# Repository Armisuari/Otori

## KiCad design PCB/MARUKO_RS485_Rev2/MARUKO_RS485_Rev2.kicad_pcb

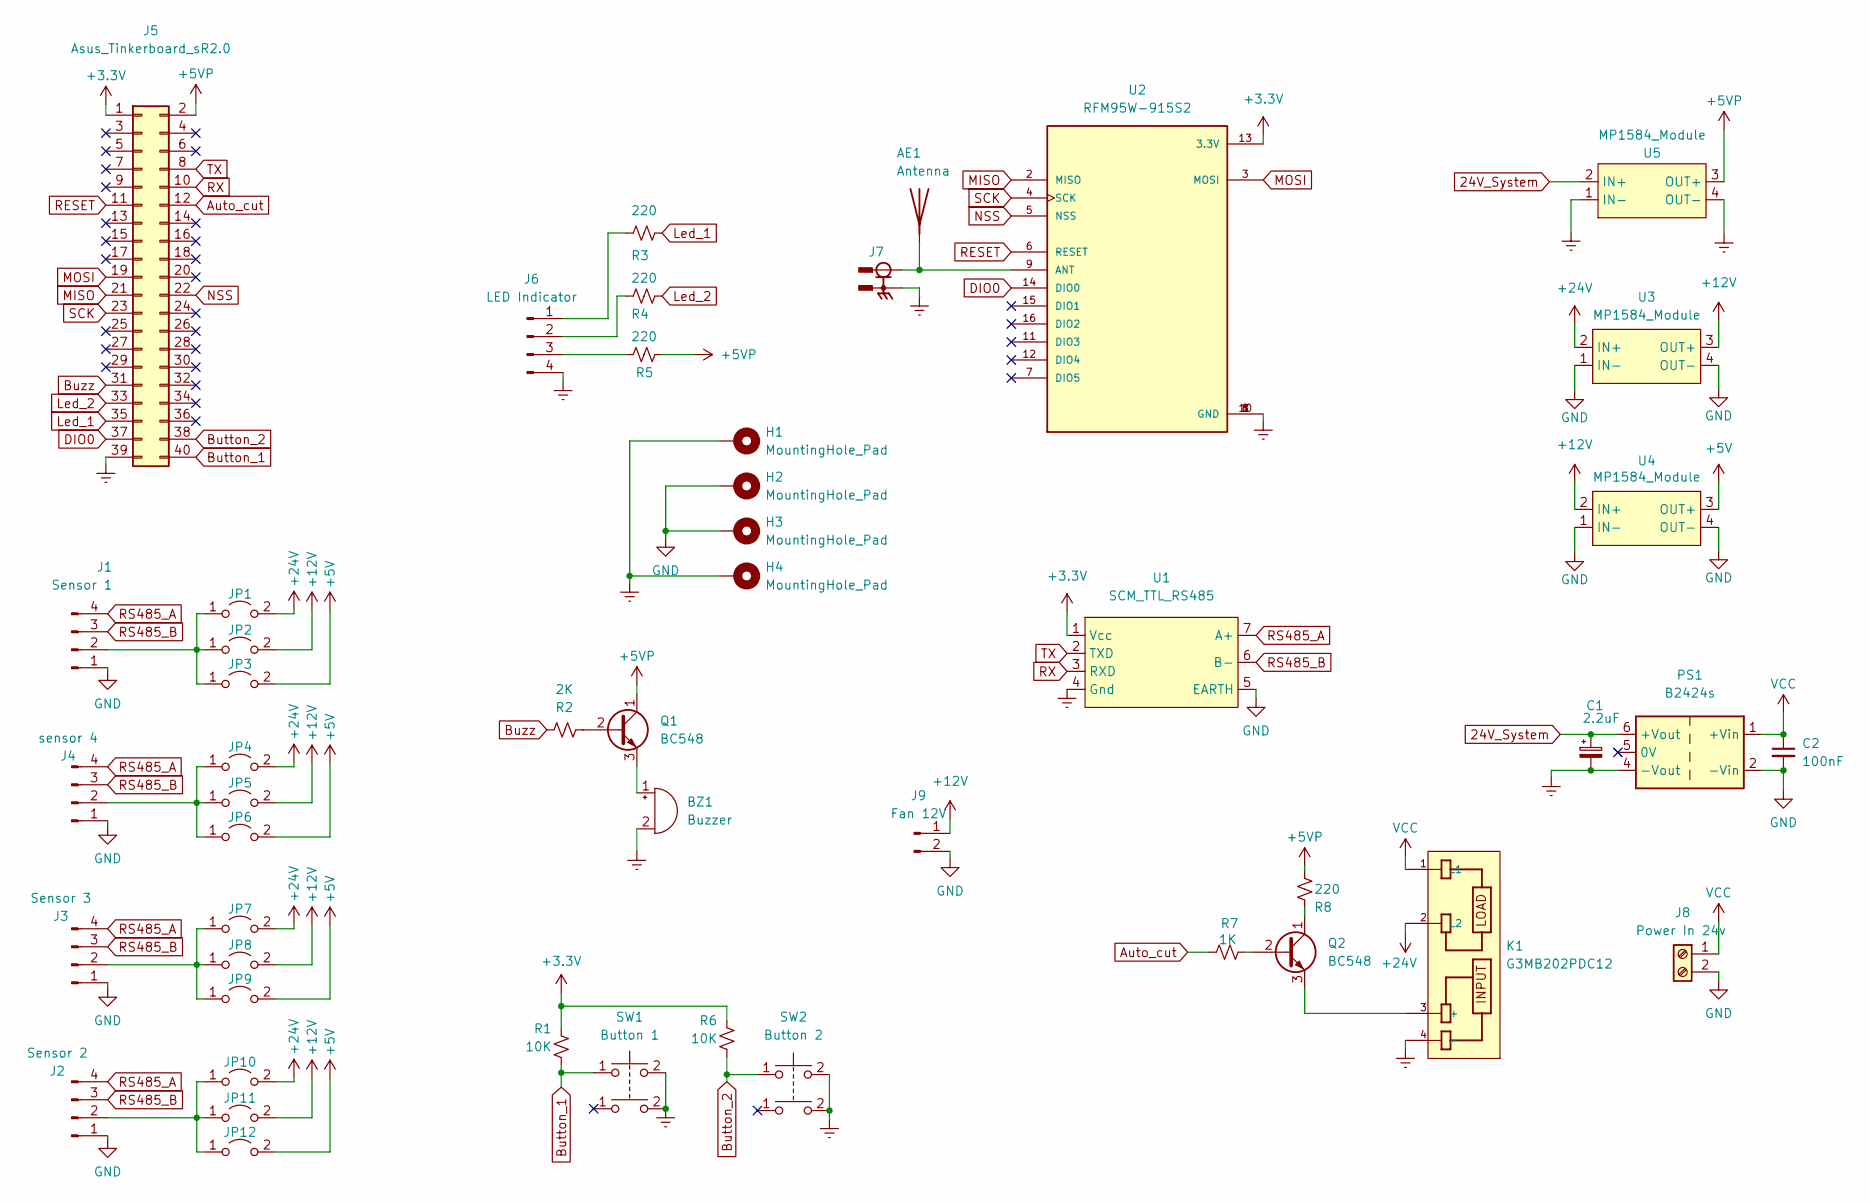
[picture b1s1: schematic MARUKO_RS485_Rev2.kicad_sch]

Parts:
AE1: Antenna
BZ1: Buzzer; Buzzer_12x9.5RM7.6
C1: 2.2uF; CP_Radial_D5.0mm_P2.50mm
C2: 100nF; C_Rect_L7.2mm_W3.5mm_P5.00mm_FKS2_FKP2_MKS2_MKP2
H1, H2, H3, H4: MountingHole_Pad; MountingHole_3.2mm_M3_Pad_Via
J1: Sensor 1; JST_XH_B4B-XH-A_1x04_P2.50mm_Vertical
J2: Sensor 2; JST_XH_B4B-XH-A_1x04_P2.50mm_Vertical
J3: Sensor 3; JST_XH_B4B-XH-A_1x04_P2.50mm_Vertical
J4: sensor 4; JST_XH_B4B-XH-A_1x04_P2.50mm_Vertical
J5: Asus_Tinkerboard_sR2.0; PinHeader_2x20_P2.54mm_Vertical
J6: LED Indicator; JST_XH_B4B-XH-A_1x04_P2.50mm_Vertical
J7: CONMHF4-SMD-G-T; LINX_CONMHF4-SMD-G-T; PARTREV A
J8: Power In 24v; TerminalBlock_Phoenix_MKDS-1,5-2-5.08_1x02_P5.08mm_Horizont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
J9: Fan 12V; JST_XH_B2B-XH-A_1x02_P2.50mm_Vertical
JP1, JP4, JP7, JP10: 24V; PinHeader_1x02_P2.54mm_Vertical
JP2, JP5, JP8, JP11: 12V; PinHeader_1x02_P2.54mm_Vertical
JP3, JP6, JP9, JP12: 5V; PinHeader_1x02_P2.54mm_Vertical
K1: G3MB202PDC12; RELAY_G3MB202PDC12; PARTREV N/A
PS1: B2424s; Converter_DCDC_XP_POWER-IHxxxxSH_THT
Q1, Q2: BC548; TO-92_Inline
R1, R6: 10K; R_Axial_DIN0207_L6.3mm_D2.5mm_P10.16mm_Horizontal
R2: 2K; R_Axial_DIN0207_L6.3mm_D2.5mm_P10.16mm_Horizontal
R3, R4, R5, R8: 220; R_Axial_DIN0207_L6.3mm_D2.5mm_P10.16mm_Horizontal
R7: 1K; R_Axial_DIN0207_L6.3mm_D2.5mm_P10.16mm_Horizontal
SW1: Button 1; SW_PUSH_6mm_H5mm
SW2: Button 2; SW_PUSH_6mm_H5mm
U1: SCM_TTL_RS485
U2: RFM95W-915S2; XCVR_RFM95W-915S2
U3, U4, U5: MP1584_Module; mo

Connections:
24V_System: C1.1, PS1.6 (+Vout), U5.2 (IN+)
+3V3: J5.1, R1.2, R6.2, U1.1 (Vcc), U2.13 (3.3V)
+5V: JP3.2 (B), JP6.2 (B), JP9.2 (B), JP12.2 (B), U4.3 (OUT+)
+5VP: J5.2, J5.4, Q1.1 (C), R5.1, R8.1, U5.3 (OUT+)
+12V: J9.1, JP2.2 (B), JP5.2 (B), JP8.2 (B), JP11.2 (B), U3.3 (OUT+), U4.2 (IN+)
+24V: JP1.2 (B), JP4.2 (B), JP7.2 (B), JP10.2 (B), K1.2 (L2), U3.2 (IN+)
Auto_cut: J5.12, R7.2
Button_1: J5.40, R1.1, SW1.1
Button_2: J5.38, R6.1, SW2.1
Buzz: J5.31, R2.1
DIO0: J5.37, U2.14 (DIO0)
Earth: BZ1.2 (+), C1.2, H1.1, H4.1, J5.39, J6.4, J7.S1, J7.S2, J7.S3, K1.4 (-), PS1.4 (-Vout), SW1.2 (4), SW2.2 (4), U1.4 (Gnd), U2.1 (GND), U2.8 (GND), U2.10 (GND), U5.1 (IN-), U5.4 (OUT-)
GND: C2.2, H2.1, H3.1, J1.1, J2.1, J3.1, J4.1, J8.2, J9.2, PS1.2 (-Vin), U1.5 (EARTH), U3.1 (IN-), U3.4 (OUT-), U4.1 (IN-), U4.4 (OUT-)
Led_1: J5.35, R3.1
Led_2: J5.33, R4.1
MISO: J5.21, U2.2 (MISO)
MOSI: J5.19, U2.3 (MOSI)
NSS: J5.22, U2.5 (NSS)
unnamed: AE1.1, J7.1, U2.9 (ANT)
unnamed: BZ1.1 (-), Q1.3 (E)
unnamed: J1.2, JP1.1 (A), JP2.1 (A), JP3.1 (A)
unnamed: J2.2, JP10.1 (A), JP11.1 (A), JP12.1 (A)
unnamed: J3.2, JP7.1 (A), JP8.1 (A), JP9.1 (A)
unnamed: J4.2, JP4.1 (A), JP5.1 (A), JP6.1 (A)
unnamed: J6.1, R3.2
unnamed: J6.2, R4.2
unnamed: J6.3, R5.2
unnamed: K1.3 (+), Q2.3 (E)
unnamed: Q1.2 (B), R2.2
unnamed: Q2.1 (C), R8.2
unnamed: Q2.2 (B), R7.1
RESET: J5.11, U2.6 (RESET)
RS485_A: J1.4, J2.4, J3.4, J4.4, U1.7 (A+)
RS485_B: J1.3, J2.3, J3.3, J4.3, U1.6 (B-)
RX: J5.10, U1.3 (RXD)
SCK: J5.23, U2.4 (SCK)
TX: J5.8, U1.2 (TXD)
VCC: C2.1, J8.1, K1.1 (L1), PS1.1 (+Vin)

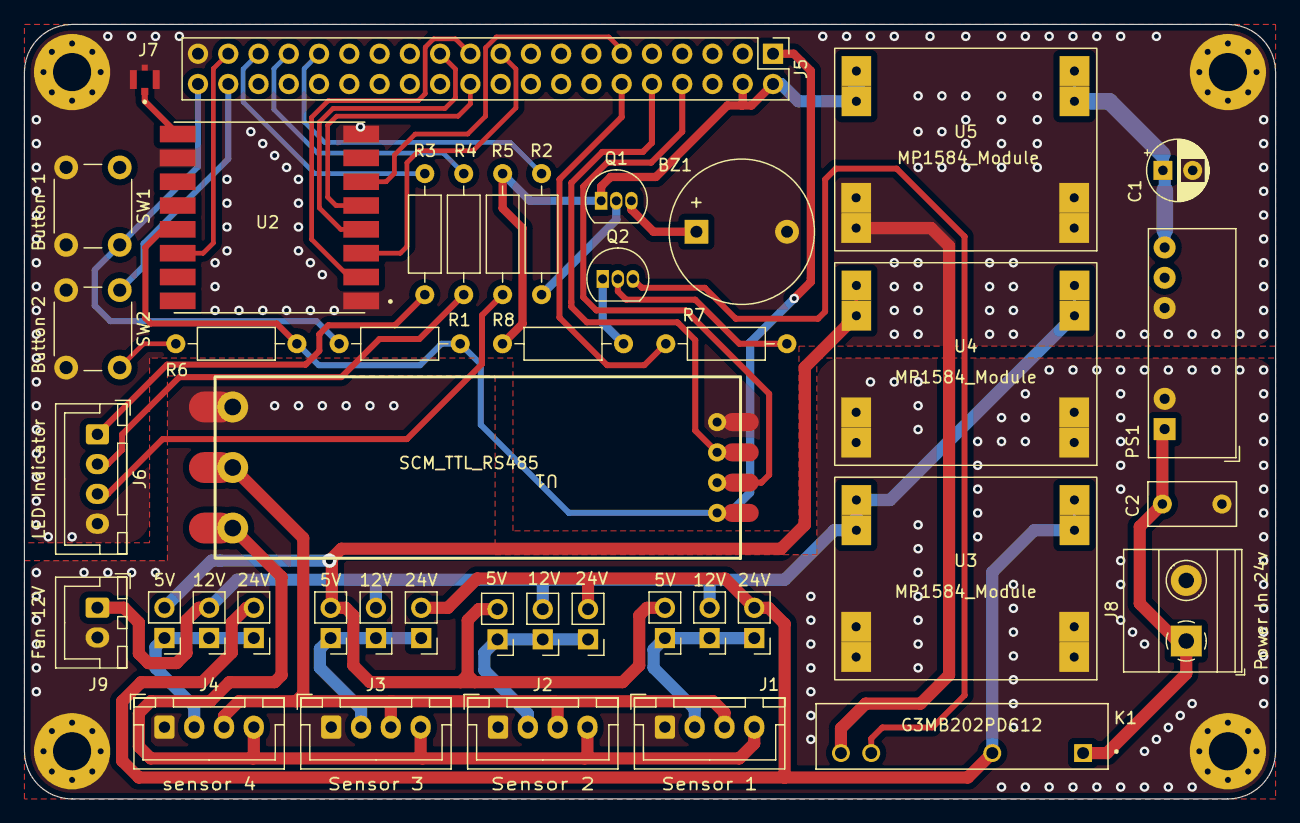
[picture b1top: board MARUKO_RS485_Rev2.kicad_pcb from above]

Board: 2 copper layers, 105.0 x 65.0 mm, 47 parts (0 on the bottom side), 38 nets.

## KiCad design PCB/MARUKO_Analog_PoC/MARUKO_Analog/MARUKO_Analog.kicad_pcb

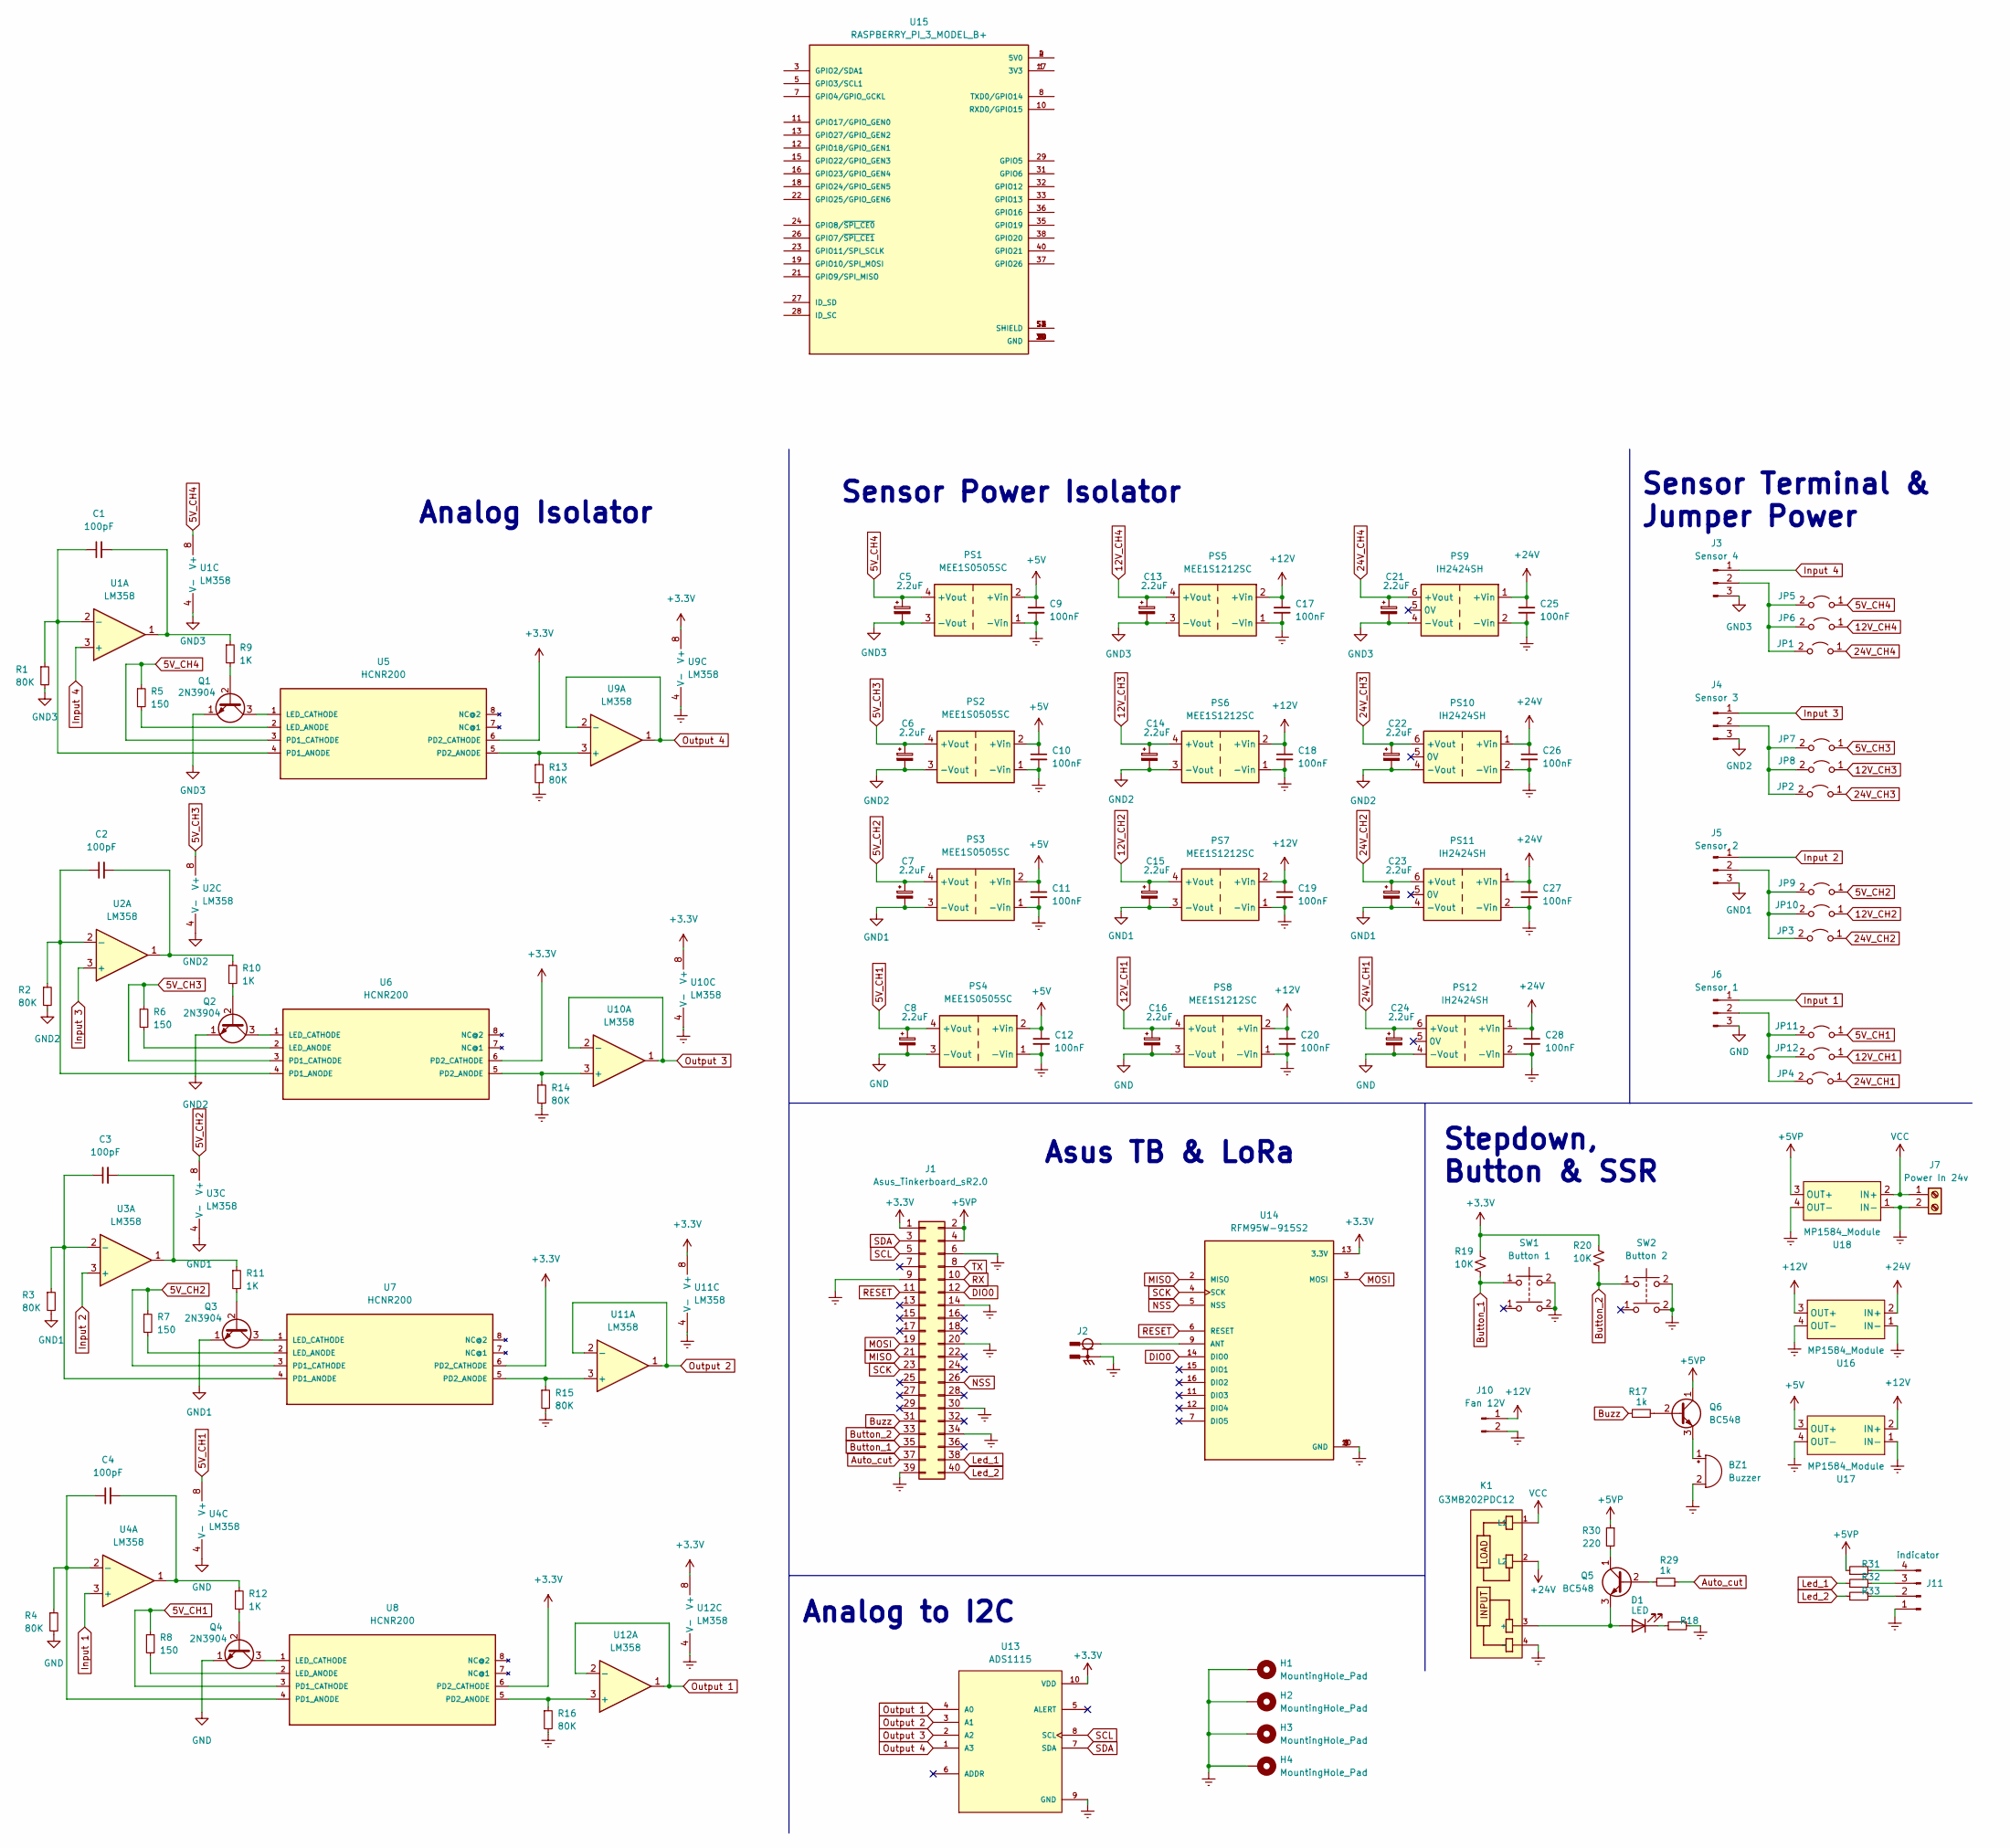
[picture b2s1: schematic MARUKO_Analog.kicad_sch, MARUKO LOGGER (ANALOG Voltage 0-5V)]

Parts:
BZ1: Buzzer; Buzzer_12x9.5RM7.6
C1, C2, C3, C4: 100pF; C_Disc_D7.5mm_W5.0mm_P7.50mm
C5, C6, C7, C8, C13, C14, C15, C16, C21, C22, C23, C24: 2.2uF; CP_Radial_D5.0mm_P2.50mm
C9, C10, C11, C12, C17, C18, C19, C20, C25, C26, C27, C28: 100nF; C_Rect_L7.2mm_W3.5mm_P5.00mm_FKS2_FKP2_MKS2_MKP2
D1: LED; LED_D3.0mm
H1, H2, H3, H4: MountingHole_Pad; MountingHole_3.2mm_M3_Pad_Via
J1: Asus_Tinkerboard_sR2.0; PinHeader_2x20_P2.54mm_Vertical
J2: CONMHF4-SMD-G-T; LINX_CONMHF4-SMD-G-T; PARTREV A
J3: Sensor 4; JST_XH_B3B-XH-A_1x03_P2.50mm_Vertical
J4: Sensor 3; JST_XH_B3B-XH-A_1x03_P2.50mm_Vertical
J5: Sensor 2; JST_XH_B3B-XH-A_1x03_P2.50mm_Vertical
J6: Sensor 1; JST_XH_B3B-XH-A_1x03_P2.50mm_Vertical
J7: Power In 24v; TerminalBlock_Phoenix_MKDS-1,5-2-5.08_1x02_P5.08mm_Horizont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
J10: Fan 12V; JST_XH_B2B-XH-A_1x02_P2.50mm_Vertical
J11: indicator; JST_XH_B4B-XH-A_1x04_P2.50mm_Vertical
JP1, JP2, JP3, JP4: 24V; PinHeader_1x02_P2.54mm_Vertical
JP5, JP7, JP9, JP11: 5V; PinHeader_1x02_P2.54mm_Vertical
JP6, JP8, JP10, JP12: 12V; PinHeader_1x02_P2.54mm_Vertical
K1: G3MB202PDC12; RELAY_G3MB202PDC12; PARTREV N/A
PS1, PS2, PS3, PS4: MEE1S0505SC; Converter_DCDC_Murata_MEE1SxxxxSC_THT
PS5, PS6, PS7, PS8: MEE1S1212SC; Converter_DCDC_Murata_MEE1SxxxxSC_THT
PS9, PS10, PS11, PS12: IH2424SH; Converter_DCDC_XP_POWER-IHxxxxSH_THT
Q1, Q2, Q3, Q4: 2N3904; TO-92_Inline
Q5, Q6: BC548; TO-92_Inline
R1, R2, R3, R4, R13, R14, R15, R16: 80K; R_Axial_DIN0207_L6.3mm_D2.5mm_P10.16mm_Horizontal
R5, R6, R7, R8: 150; R_Axial_DIN0207_L6.3mm_D2.5mm_P10.16mm_Horizontal
R9, R10, R11, R12: 1K; R_Axial_DIN0207_L6.3mm_D2.5mm_P10.16mm_Horizontal
R17, R29: 1k; R_Axial_DIN0207_L6.3mm_D2.5mm_P10.16mm_Horizontal
R18, R19, R20, R32, R33: 10K; R_Axial_DIN0207_L6.3mm_D2.5mm_P10.16mm_Horizontal
R30, R31: 220; R_Axial_DIN0207_L6.3mm_D2.5mm_P10.16mm_Horizontal
SW1: Button 1; SW_PUSH_6mm_H5mm
SW2: Button 2; SW_PUSH_6mm_H5mm
U1, U2, U3, U4, U9, U10, U11, U12: LM358; DIP-8_W7.62mm
U5, U6, U7, U8: HCNR200; DIP1016W48P254L1130H510Q8
U13: ADS1115; MODULE_ZC261500; PARTREV NA
U14: RFM95W-915S2; XCVR_RFM95W-915S2
U15: RASPBERRY_PI_3_MODEL_B+; MODULE_RASPBERRY_PI_3_MODEL_B+; PARTREV 1.0
U16, U17, U18: MP1584_Module; mo

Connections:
5V_CH1: C8.1, JP11.1 (A), PS4.4 (+Vout), R8.1, U4.8 (V+), U8.3 (PD1_CATHODE)
5V_CH2: C7.1, JP9.1 (A), PS3.4 (+Vout), R7.1, U3.8 (V+), U7.3 (PD1_CATHODE)
5V_CH3: C6.1, JP7.1 (A), PS2.4 (+Vout), R6.1, U2.8 (V+), U6.3 (PD1_CATHODE)
5V_CH4: C5.1, JP5.1 (A), PS1.4 (+Vout), R5.1, U1.8 (V+), U5.3 (PD1_CATHODE)
12V_CH1: C16.1, JP12.1 (A), PS8.4 (+Vout)
12V_CH2: C15.1, JP10.1 (A), PS7.4 (+Vout)
12V_CH3: C14.1, JP8.1 (A), PS6.4 (+Vout)
12V_CH4: C13.1, JP6.1 (A), PS5.4 (+Vout)
24V_CH1: C24.1, JP4.1 (A), PS12.6 (+Vout)
24V_CH2: C23.1, JP3.1 (A), PS11.6 (+Vout)
24V_CH3: C22.1, JP2.1 (A), PS10.6 (+Vout)
24V_CH4: C21.1, JP1.1 (A), PS9.6 (+Vout)
+3V3: J1.1, R19.2, R20.2, U5.6 (PD2_CATHODE), U6.6 (PD2_CATHODE), U7.6 (PD2_CATHODE), U8.6 (PD2_CATHODE), U9.8 (V+), U10.8 (V+), U11.8 (V+), U12.8 (V+), U13.10 (VDD), U14.13 (3.3V)
+5V: C9.1, C10.1, C11.1, C12.1, PS1.2 (+Vin), PS2.2 (+Vin), PS3.2 (+Vin), PS4.2 (+Vin), U17.3 (OUT+)
+5VP: J1.2, J1.4, Q6.1 (C), R30.1, R31.1, U18.3 (OUT+)
+12V: C17.1, C18.1, C19.1, C20.1, J10.1, PS5.2 (+Vin), PS6.2 (+Vin), PS7.2 (+Vin), PS8.2 (+Vin), U16.3 (OUT+), U17.2 (IN+)
+24V: C25.1, C26.1, C27.1, C28.1, K1.2 (L2), PS9.1 (+Vin), PS10.1 (+Vin), PS11.1 (+Vin), PS12.1 (+Vin), U16.2 (IN+)
Auto_cut: J1.37, R29.1
Button_1: J1.35, R19.1, SW1.1
Button_2: J1.33, R20.1, SW2.1
Buzz: J1.31, R17.1
DIO0: J1.12, U14.14 (DIO0)
Earth: BZ1.2 (+), C9.2, C10.2, C11.2, C12.2, C17.2, C18.2, C19.2, C20.2, C25.2, C26.2, C27.2, C28.2, H1.1, H2.1, H3.1, H4.1, J1.6, J1.9, J1.14, J1.20, J1.30, J1.34, J1.39, J2.S1, J2.S2, J2.S3, J7.2, J10.2, J11.1, K1.4 (-), PS1.1 (-Vin), PS2.1 (-Vin), PS3.1 (-Vin), PS4.1 (-Vin), PS5.1 (-Vin), PS6.1 (-Vin), PS7.1 (-Vin), PS8.1 (-Vin), PS9.2 (-Vin), PS10.2 (-Vin), PS11.2 (-Vin), PS12.2 (-Vin), R13.2, R14.2, R15.2, R16.2, R18.2, SW1.2 (4), SW2.2, U9.4 (V-), U10.4 (V-), U11.4 (V-), U12.4 (V-), U13.9 (GND), U14.1 (GND), U14.8 (GND), U14.10 (GND), U16.1 (IN-), U16.4 (OUT-), U17.1 (IN-), U17.4 (OUT-), U18.1 (IN-), U18.4 (OUT-)
GND: C8.2, C16.2, C24.2, J6.3, PS4.3 (-Vout), PS8.3 (-Vout), PS12.4 (-Vout), Q4.1 (E), R4.2, U4.4 (V-)
GND1: C7.2, C15.2, C23.2, J5.3, PS3.3 (-Vout), PS7.3 (-Vout), PS11.4 (-Vout), Q3.1 (E), R3.2, U3.4 (V-)
GND2: C6.2, C14.2, C22.2, J4.3, PS2.3 (-Vout), PS6.3 (-Vout), PS10.4 (-Vout), Q2.1 (E), R2.2, U2.4 (V-)
GND3: C5.2, C13.2, C21.2, J3.3, PS1.3 (-Vout), PS5.3 (-Vout), PS9.4 (-Vout), Q1.1 (E), R1.2, U1.4 (V-)
Input 1: J6.1, U4.3 (+)
Input 2: J5.1, U3.3 (+)
Input 3: J4.1, U2.3 (+)
Input 4: J3.1, U1.3 (+)
Led_1: J1.38, R32.1
Led_2: J1.40, R33.1
MISO: J1.21, U14.2 (MISO)
MOSI: J1.19, U14.3 (MOSI)
NSS: J1.26, U14.5 (NSS)
unnamed: BZ1.1 (-), Q6.3 (E)
unnamed: C1.1, R1.1, U1.2 (-), U5.4 (PD1_ANODE)
unnamed: C1.2, R9.1, U1.1
unnamed: C2.1, R2.1, U2.2 (-), U6.4 (PD1_ANODE)
unnamed: C2.2, R10.1, U2.1
unnamed: C3.1, R3.1, U3.2 (-), U7.4 (PD1_ANODE)
unnamed: C3.2, R11.1, U3.1
unnamed: C4.1, R4.1, U4.2 (-), U8.4 (PD1_ANODE)
unnamed: C4.2, R12.1, U4.1
unnamed: D1.1 (K), R18.1
unnamed: D1.2 (A), K1.3 (+), Q5.3 (E)
unnamed: J2.1, U14.9 (ANT)
unnamed: J3.2, JP1.2 (B), JP5.2 (B), JP6.2 (B)
unnamed: J4.2, JP2.2 (B), JP7.2 (B), JP8.2 (B)
unnamed: J5.2, JP3.2 (B), JP9.2 (B), JP10.2 (B)
unnamed: J6.2, JP4.2 (B), JP11.2 (B), JP12.2 (B)
unnamed: Q1.2 (B), R9.2
unnamed: Q1.3 (C), U5.1 (LED_CATHODE)
unnamed: Q2.2 (B), R10.2
unnamed: Q2.3 (C), U6.1 (LED_CATHODE)
unnamed: Q3.2 (B), R11.2
unnamed: Q3.3 (C), U7.1 (LED_CATHODE)
unnamed: Q4.2 (B), R12.2
unnamed: Q4.3 (C), U8.1 (LED_CATHODE)
unnamed: Q6.2 (B), R17.2
unnamed: R5.2, U5.2 (LED_ANODE)
unnamed: R6.2, U6.2 (LED_ANODE)
unnamed: R7.2, U7.2 (LED_ANODE)
unnamed: R8.2, U8.2 (LED_ANODE)
unnamed: R13.1, U5.5 (PD2_ANODE), U9.3 (+)
unnamed: R14.1, U6.5 (PD2_ANODE), U10.3 (+)
unnamed: R15.1, U7.5 (PD2_ANODE), U11.3 (+)
unnamed: R16.1, U8.5 (PD2_ANODE), U12.3 (+)
unnamed: Q5.2 (B), R29.2
unnamed: Q5.1 (C), R30.2
unnamed: J11.4, R31.2
unnamed: J11.3, R32.2
unnamed: J11.2, R33.2
unnamed: U15.1 (3V3), U15.17 (3V3)
unnamed: U15.2 (5V0), U15.4 (5V0)
unnamed: U15.6 (GND), U15.9 (GND), U15.14 (GND), U15.20 (GND), U15.25 (GND), U15.30 (GND), U15.34 (GND), U15.39 (GND)
unnamed: U15.S1 (SHIELD), U15.S2 (SHIELD), U15.S3 (SHIELD), U15.S4 (SHIELD)
Output 1: U12.1, U12.2 (-), U13.4 (A0)
Output 2: U11.1, U11.2 (-), U13.3 (A1)
Output 3: U10.1, U10.2 (-), U13.2 (A2)
Output 4: U9.1, U9.2 (-), U13.1 (A3)
RESET: J1.11, U14.6 (RESET)
RX: J1.10
SCK: J1.23, U14.4 (SCK)
SCL: J1.5, U13.8 (SCL)
SDA: J1.3, U13.7 (SDA)
TX: J1.8
VCC: J7.1, K1.1 (L1), U18.2 (IN+)

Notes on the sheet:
Asus TB & LoRa
Analog Isolator
Sensor Power Isolator
Analog to I2C
Stepdown, Button & SSR
Sensor Terminal & Jumper Power

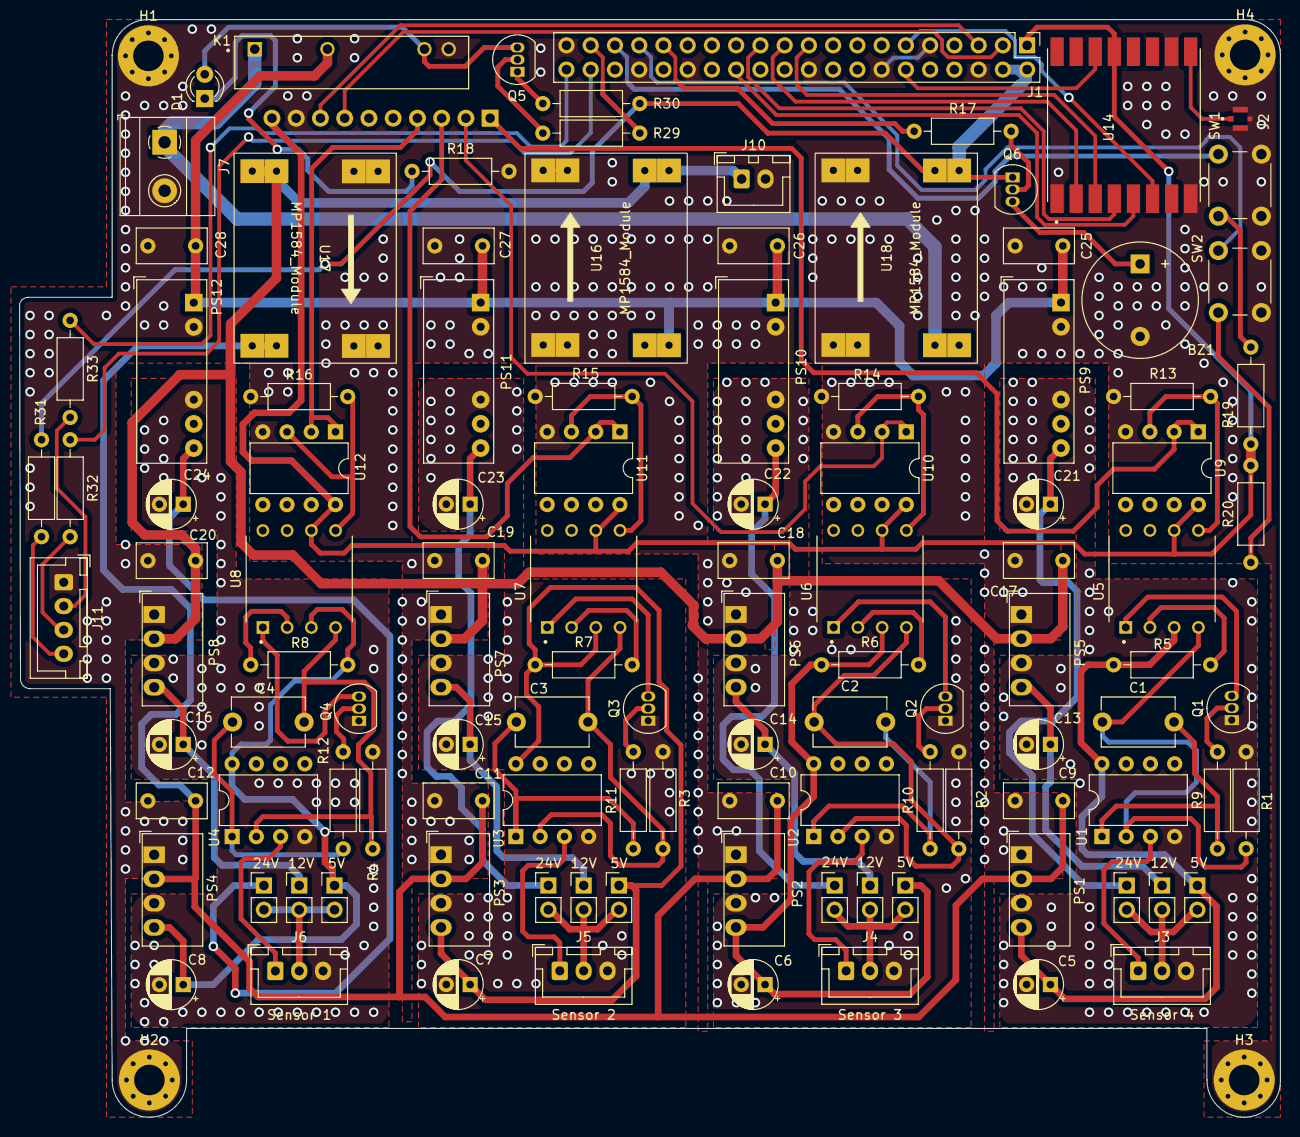
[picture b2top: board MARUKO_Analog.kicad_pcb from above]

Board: 2 copper layers, 132.1 x 115.0 mm, 118 parts (1 on the bottom side), 83 nets.

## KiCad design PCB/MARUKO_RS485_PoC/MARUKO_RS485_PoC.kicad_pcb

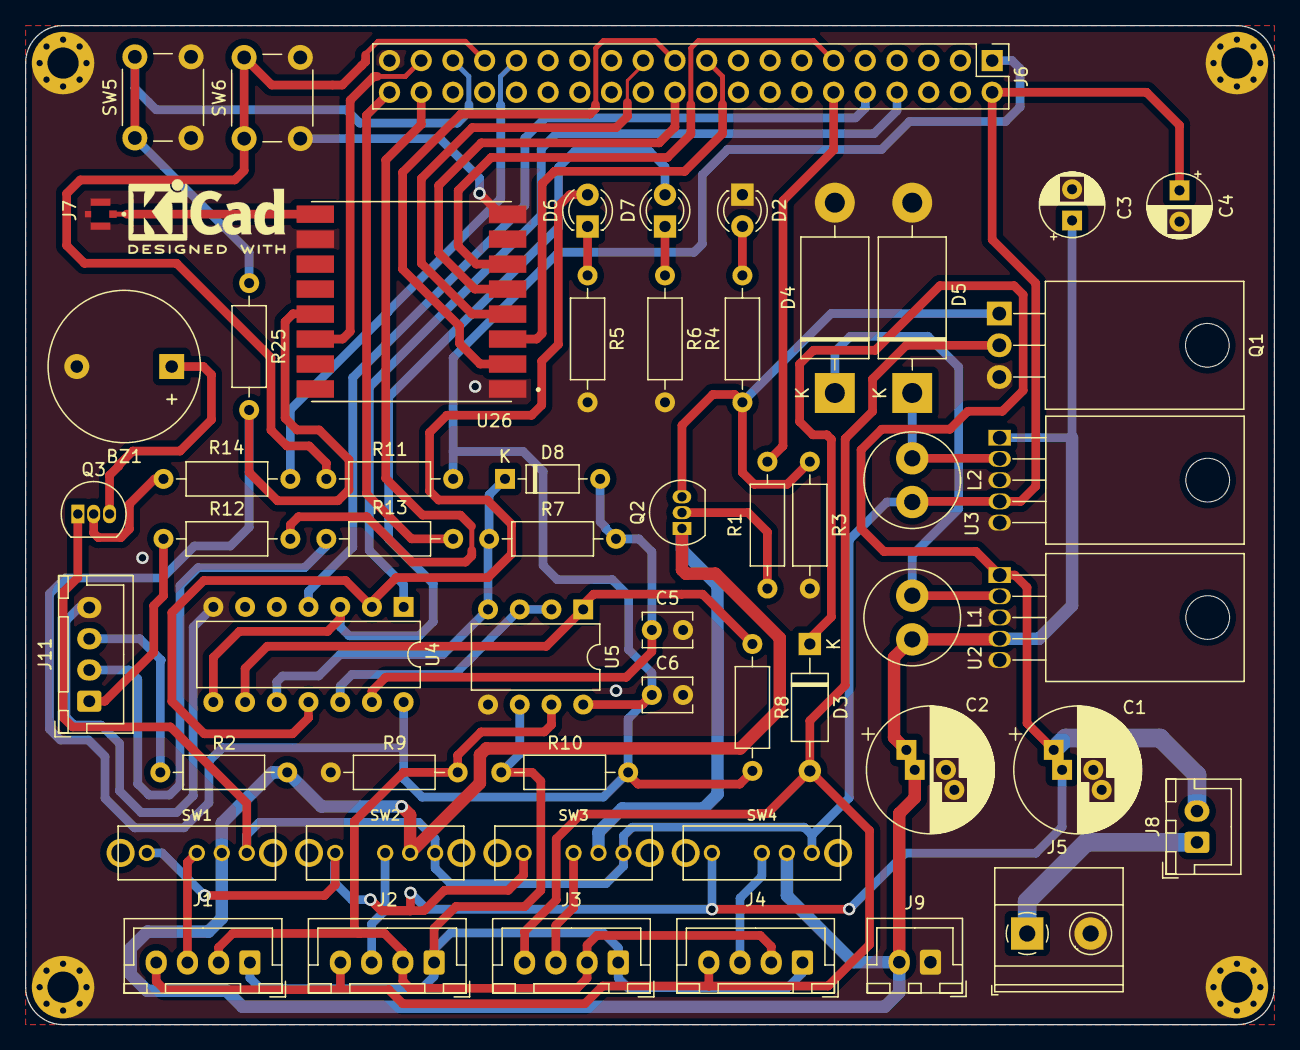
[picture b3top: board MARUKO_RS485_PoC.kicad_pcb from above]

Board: 2 copper layers, 100.0 x 80.0 mm, 59 parts (0 on the bottom side), 46 nets.

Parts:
BZ1: Buzzer; Buzzer_12x9.5RM7.6
C1: 220uF / 25V; CP_Radial_D10.0mm_P2.50mm_P5.00mm
C2: 680uF / 16V; CP_Radial_D10.0mm_P2.50mm_P5.00mm
C3, C4: 220uF / 16V; CP_Radial_D5.0mm_P2.50mm
C5, C6: 0.1uF; C_Disc_D3.8mm_W2.6mm_P2.50mm
D2, D6, D7: LED; LED_D3.0mm
D3: D_Small; D_A-405_P10.16mm_Horizontal
D4, D5: 1N5820; D_DO-201AD_P15.24mm_Horizontal
D8: 1N4148; D_DO-35_SOD27_P7.62mm_Horizontal
H1, H2, H3, H4: MountingHole_Pad; MountingHole_2.5mm_Pad_Via
J1: Sensor_conn1; JST_XH_B4B-XH-A_1x04_P2.50mm_Vertical
J2: Sensor_conn2; JST_XH_B4B-XH-A_1x04_P2.50mm_Vertical
J3: Sensor_conn3; JST_XH_B4B-XH-A_1x04_P2.50mm_Vertical
J4: Sensor_conn4; JST_XH_B4B-XH-A_1x04_P2.50mm_Vertical
J5: Power In 24V; TerminalBlock_Phoenix_MKDS-1,5-2-5.08_1x02_P5.08mm_Horizont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
J6: Asus_Tinkerboard_sR2.0; PinHeader_2x20_P2.54mm_Vertical
J7: CONMHF4-SMD-G-T; LINX_CONMHF4-SMD-G-T
J8: Switch; JST_XH_B2B-XH-A_1x02_P2.50mm_Vertical
J9: Fan 12v; JST_XH_B2B-XH-A_1x02_P2.50mm_Vertical
J11: Conn_01x04_Male; JST_XH_B4B-XH-A_1x04_P2.50mm_Vertical
L1, L2: 33uH; L_Radial_D7.5mm_P3.50mm_Fastron_07P
Q1: IRLZ44N; TO-220-3_Horizontal_TabDown
Q2, Q3: BC548; TO-92_Inline
R1, R14: 2K; R_Axial_DIN0207_L6.3mm_D2.5mm_P10.16mm_Horizontal
R2, R4, R8, R9, R10: 4.7K; R_Axial_DIN0207_L6.3mm_D2.5mm_P10.16mm_Horizontal
R3, R11, R25: 10K; R_Axial_DIN0207_L6.3mm_D2.5mm_P10.16mm_Horizontal
R5, R6: 2.4k; R_Axial_DIN0207_L6.3mm_D2.5mm_P10.16mm_Horizontal
R7: 56k; R_Axial_DIN0207_L6.3mm_D2.5mm_P10.16mm_Horizontal
R12, R13: 220; R_Axial_DIN0207_L6.3mm_D2.5mm_P10.16mm_Horizontal
SW1, SW2, SW3, SW4: SW_SP3T; OS102011MS8QP1
SW5, SW6: Button; SW_PUSH_6mm_H5mm
U2: LM2596T-12; TO-220-5_Horizontal_TabDown
U3: LM2596T-5; TO-220-5_Horizontal_TabDown
U4: 74HC14; DIP-14_W7.62mm
U5: MAX485E; DIP-8_W7.62mm
U26: RFM95W-915S2; XCVR_RFM95W-915S2

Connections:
+3V3: C6.1, J6.1, R8.2, R10.1, R11.2, R25.2, U4.14 (VCC), U5.8 (VCC), U26.13 (3.3V)
+5V: C4.1, J6.2, L2.2, Q3.1 (C), SW1.4, SW2.4, SW3.4, SW4.4, U3.4 (FB)
+12V: C2.1, C3.1, J9.2, L1.2, Q2.1 (C), R2.1, SW1.3, SW2.3, SW3.3, SW4.3, U2.4 (FB), U3.1 (VIN)
+24V: C1.1, D3.1 (K), J8.2, SW1.1, SW2.1, SW3.1, SW4.1, U2.1 (VIN)
Auto_cut: J6.12, R1.1
Button_1: J6.35, R25.1, SW5.1
Button_2: J6.33, R11.1, SW6.1
Buzz: J6.31, R14.1
DIO0: J6.37, U26.14 (DIO0)
GND: BZ1.2 (+), C1.2, C2.2, C3.2, C4.2, C5.2, C6.2, D2.1 (K), D4.2 (A), D5.2 (A), H1.1, H2.1, H3.1, H4.1, J5.2, J6.39, J7.S1, J7.S2, J7.S3, J9.1, J11.4, Q1.3 (S), R3.2, R5.2, R6.2, R9.2, SW5.2, SW6.2, U2.3 (GND), U2.5 (~ON/OFF), U3.3 (GND), U3.5 (~ON/OFF), U4.7 (GND), U5.5 (GND), U26.1 (GND), U26.8 (GND), U26.10 (GND)
GNDD: D3.2 (A), J1.4, J2.4, J3.4, J4.4, Q1.2 (D)
Led_1: J6.38, R12.1
Led_2: J6.40, R13.1
MISO: J6.21, U26.2 (MISO)
MOSI: J6.19, U26.3 (MOSI)
NSS: J6.22, U26.5 (NSS)
unnamed: J7.1, U26.9 (ANT)
unnamed: BZ1.1 (-), Q3.3 (E)
unnamed: C5.1, D8.2 (A), R7.2, U4.13
unnamed: D2.2 (A), R4.2
unnamed: D4.1 (K), L1.1, U2.2 (OUT)
unnamed: D5.1 (K), L2.1, U3.2 (OUT)
unnamed: D6.1 (K), R5.1
unnamed: D6.2 (A), U4.2, U4.11
unnamed: D7.1 (K), R6.1
unnamed: D7.2 (A), U4.3, U4.8
unnamed: D8.1 (K), R7.1, U4.10, U5.4 (DI)
unnamed: J1.3, SW1.2
unnamed: J2.3, SW2.2
unnamed: J3.3, SW3.2
unnamed: J4.3, SW4.2
unnamed: J11.1, R12.2
unnamed: J11.2, R13.2
unnamed: J11.3, R2.2
unnamed: Q1.1 (G), Q2.3 (E), R3.1, R4.1
unnamed: Q2.2 (B), R1.2
unnamed: Q3.2 (B), R14.2
unnamed: R8.1, U4.9, U5.1 (RO)
unnamed: U4.12, U5.2 (~RE), U5.3 (DE)
RESET: J6.11, U26.6 (RESET)
RS485_A: J1.1, J2.1, J3.1, J4.1, R10.2, U5.6 (A)
RS485_B: J1.2, J2.2, J3.2, J4.2, R9.1, U5.7 (B)
RX: J6.10, U4.4
SCK: J6.23, U26.4 (SCK)
TX: J6.8, U4.1
VCC: J5.1, J8.1

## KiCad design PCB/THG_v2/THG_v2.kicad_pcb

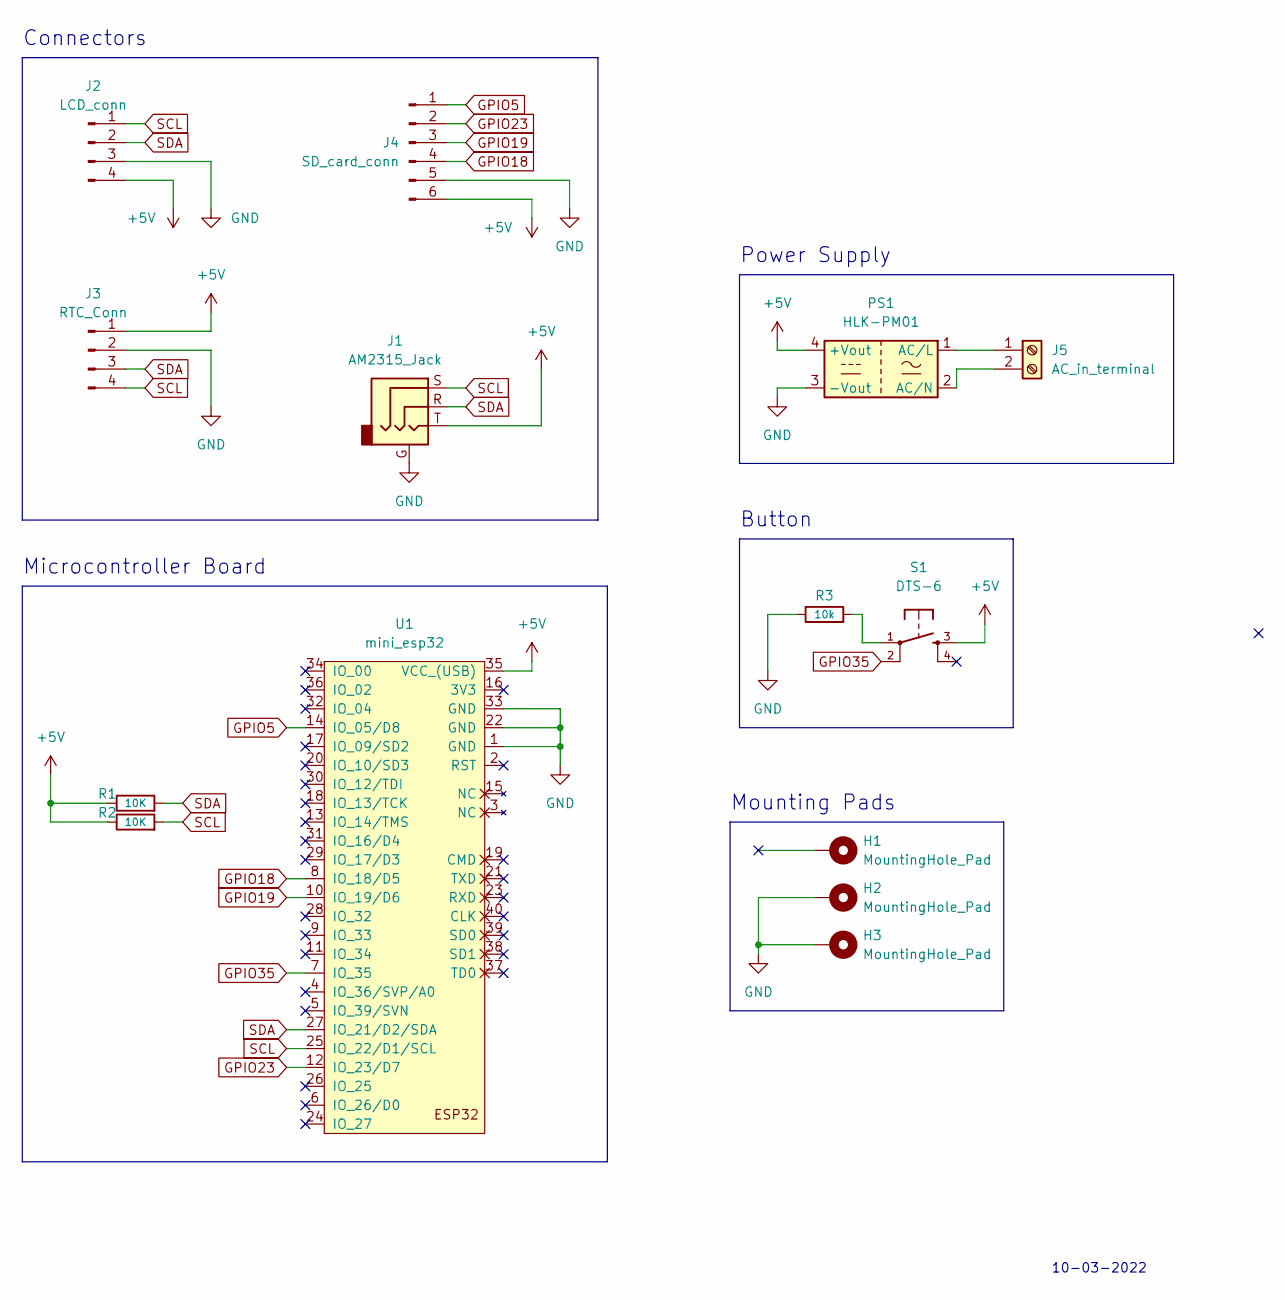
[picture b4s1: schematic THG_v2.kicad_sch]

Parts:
H1, H2, H3: MountingHole_Pad; MountingHole_2.2mm_M2_Pad_Via
J1: AM2315_Jack; TRRS-PJ-320A
J2: LCD_conn; JST_EH_B4B-EH-A_1x04_P2.50mm_Vertical
J3: RTC_Conn; JST_EH_B4B-EH-A_1x04_P2.50mm_Vertical
J4: SD_card_conn; JST_EH_B6B-EH-A_1x06_P2.50mm_Vertical
J5: AC_in_terminal; TerminalBlock_Phoenix_MKDS-1,5-2-5.08_1x02_P5.08mm_Horizont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
PS1: HLK-PM01; Converter_ACDC_HiLink_HLK-PMxx
R1, R2: 10K; R_Axial_DIN0207_L6.3mm_D2.5mm_P10.16mm_Horizontal
R3: 10k; R_Axial_DIN0207_L6.3mm_D2.5mm_P10.16mm_Horizontal
S1: DTS-6
U1: mini_esp32; ESP32_mini

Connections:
+5V: J1.T, J2.4, J3.1, J4.6, PS1.4 (+Vout), R1.1, R2.1, S1.3, U1.35 (VCC_(USB))
GND: H2.1, H3.1, J1.G, J2.3, J3.2, J4.5, PS1.3 (-Vout), R3.1, U1.1 (GND), U1.22 (GND), U1.33 (GND)
GPIO5: J4.1, U1.14 (IO_05/D8)
GPIO18: J4.4, U1.8 (IO_18/D5)
GPIO19: J4.3, U1.10 (IO_19/D6)
GPIO23: J4.2, U1.12 (IO_23/D7)
GPIO35: S1.2, U1.7 (IO_35)
unnamed: J5.1, PS1.1 (AC/L)
unnamed: J5.2, PS1.2 (AC/N)
unnamed: R3.2, S1.1
SCL: J1.S, J2.1, J3.4, R2.2, U1.25 (IO_22/D1/SCL)
SDA: J1.R, J2.2, J3.3, R1.2, U1.27 (IO_21/D2/SDA)

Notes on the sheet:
Microcontroller Board
Connectors
Power Supply
Button
10-03-2022
Mounting Pads

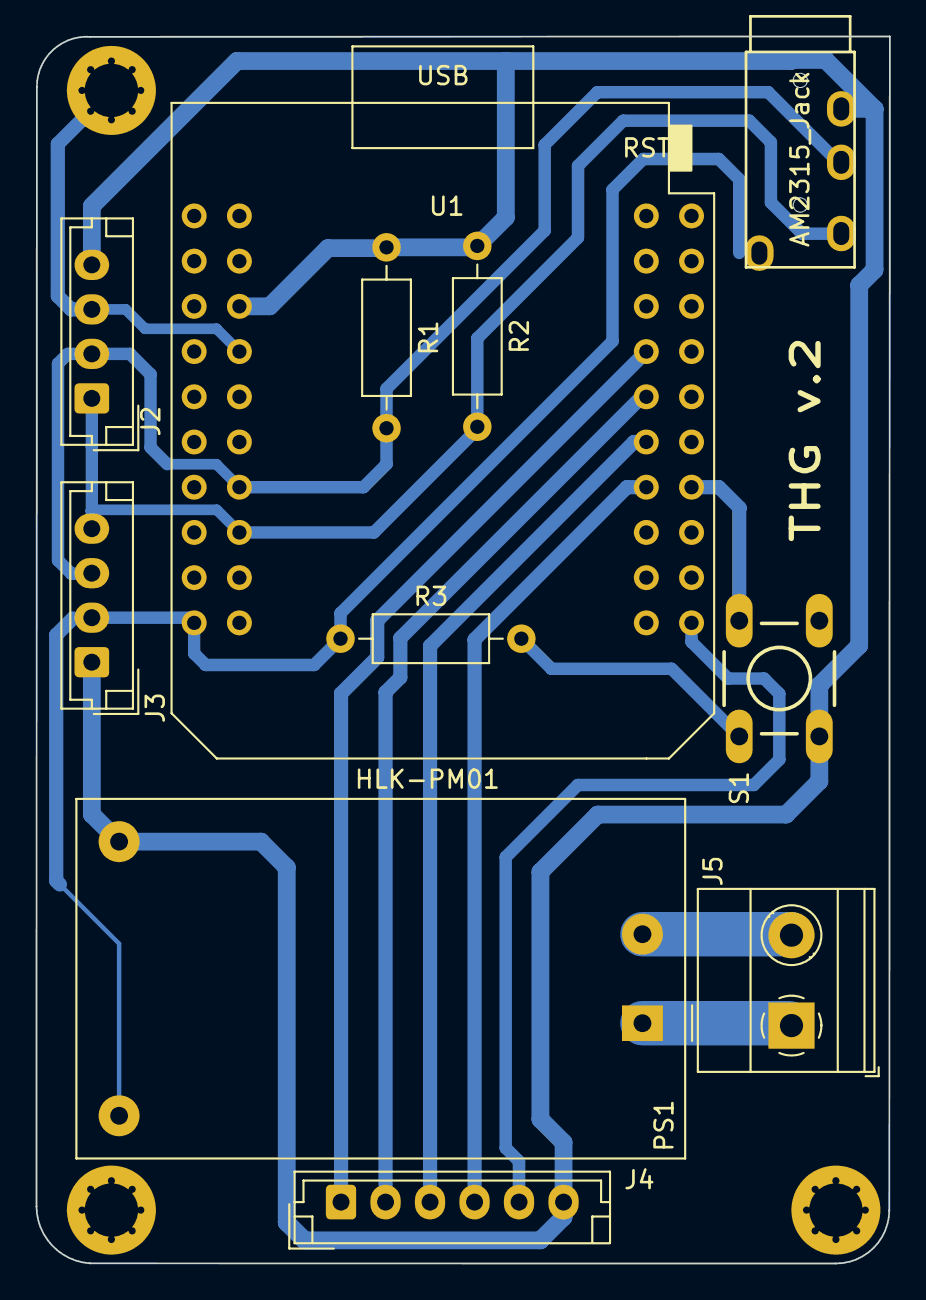
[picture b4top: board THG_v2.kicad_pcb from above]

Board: 2 copper layers, 47.9 x 68.9 mm, 14 parts (0 on the bottom side), 12 nets.
